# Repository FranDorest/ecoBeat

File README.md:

# EndeF-ecoBeat
EcoBeat is a device that measures the energy consumption by means of pulses. These pulses are generated by measuring equipment such as electricity, water or gas meters. EcoBeat translates the pulses to the corresponding units and transmits them via WIFI to a server on the Internet. This device complies with the Internet of Things standards and is specially designed to make energy measurements

# cable connection

## Optical pulse
- The pulse happens when the Interruption(6) is conected to  VCC(2)
- Interruption(6) -> pulldown

## Mechanical pulse
- The pulse happens when the Interruption(6) is conected to GND(5) 
- Interruption(6) -> pullup

## PCB Modification 
- 10K is disconected from GND and conected to Vcc

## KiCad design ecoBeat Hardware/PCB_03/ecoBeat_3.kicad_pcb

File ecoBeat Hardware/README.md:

# PCB ecoBeat 3

Se ha creado una nueva PCB que se adapta a las medidas de una caja de montaje en carril DIN.

### Materiales

A continuación aparecen los materiales que se necesitarán para construir la placa *ecoBeat*.

* [Soldador] 
* [Estaño]
* [Pinzas]
* [ESP 12 F](https://www.elecrow.com/download/ESP-12F.pdf) - Microcontrolador de 32-bit 
* [ATtiny 85](http://www.farnell.com/datasheets/1698186.pdf) - Microcontrolador de 8-bit
* [LM1117 3.3v](http://www.ti.com/lit/ds/symlink/lm1117.pdf) - Regulador de voltaje 15v - 3.3v 800mA
* [RJ45 8P8P Female](https://es.rs-online.com/web/p/conectores-rj45/2578814/) - Conector RJ45
* [2x Pulsador](https://www.adafruit.com/product/367) - Pulsador 6x6mm
* [4x 10k R](https://es.rs-online.com/web/p/resistencias-fijas-de-orificio-pasante/7077745/) - Resistencia 10k 1/4W
* [3x 220 R](https://es.rs-online.com/web/p/resistencias-fijas-de-orificio-pasante/7077612/) - Resistencia 220 1/4W
* [1x 12k R](https://es.rs-online.com/web/p/resistencias-fijas-de-orificio-pasante/7077735/) - Resistencia 12k 1/4W
* [1x 6.8k R](https://es.rs-online.com/web/p/resistencias-fijas-de-orificio-pasante/7077735/) - Resistencia 6.8k 1/4W
* [2x 10uF C](https://es.rs-online.com/web/p/condensadores-de-aluminio/0117035/) - Condensador electrolítico 10uF 50v
* [1x 100nF C](https://es.rs-online.com/web/p/condensadores-ceramicos-multicapa/5373707/) - Condensador cerámico 100nF 50v
* [1x Diodo](https://es.rs-online.com/web/p/products/7965985/?tpr=1) - Diodo 1A
* [3x LED](https://es.rs-online.com/web/p/led-visibles/2285944/) - LED 3mm
* [Pin macho 2.54mm](https://es.rs-online.com/web/p/conectores-macho-para-pcb/5473166/) - Tira pin Macho 2.54mm
* [Pin macho 2mm](https://es.rs-online.com/web/p/conectores-macho-para-pcb/6813293/) - Tira pin Macho 2mm
* [Pin hembra 2mm](https://es.rs-online.com/web/p/conectores-hembra-para-pcb/6058774/) - Tira pin hembra 2mm

### Montaje

*

## Herramientas

* [KiCad 4.0.2](http://kicad-pcb.org/) - Diseño electrónico

## Consumos

*Se ha realizado una prueba para conocer los consumos del equipo en todos sus modos de trabajo en su versión de 5V.

Modo | Con LEDs | Sin LEDs | Un
--- | --- | --- | ---
AP | 87 - 88 | 85-86 | mA 
--- | --- | --- | ---
STA + AP | 87 - 88 | 85-86 | mA
--- | --- | --- | ---
STA |85.5 - 86.5 | 3.5 - 84.5 | mA
--- | --- | --- | ---
Transmisión | 86.5 - 87.5 | 84.5 - 85.5 | mA

*Vmax 12V. El regulador se calentará hasta los 65ºC y consumirá 84,5mA.

## Autores

* **Francisco Doreste** 
* **Oscar Pujal** 

## Licencia

Este proyecto se encuentra bajo licencia GPL.

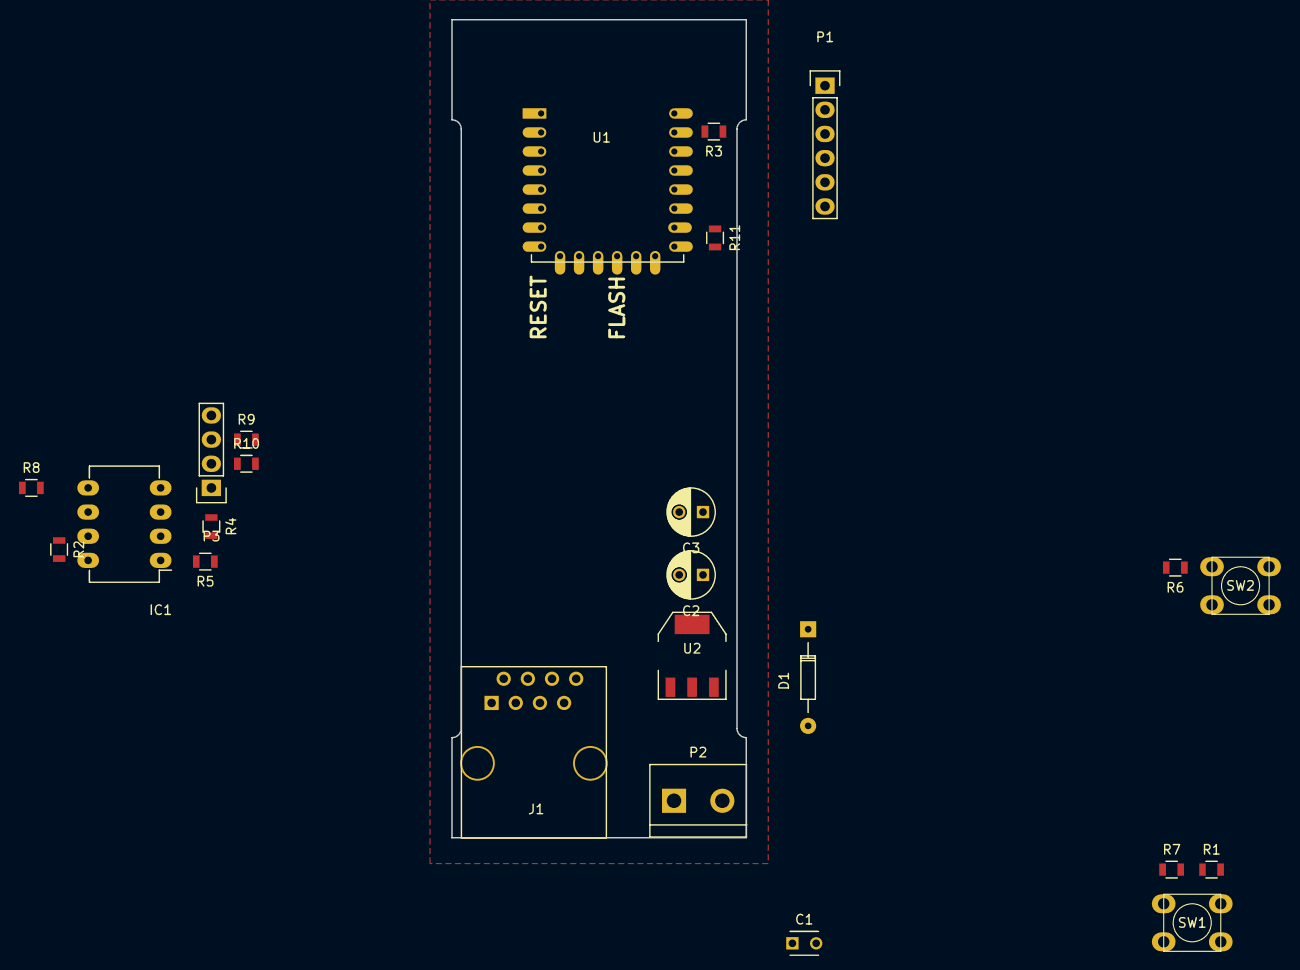
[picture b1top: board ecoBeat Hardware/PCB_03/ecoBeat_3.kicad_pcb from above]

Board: 2 copper layers, 30.9 x 86.0 mm, 24 parts (0 on the bottom side), 19 nets, no tracks yet.

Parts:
C1: 100nF; C_Disc_D3_P2.5
C2, C3: 10uF; C_Radial_D5_L6_P2.5
D1: D; Diode_DO-35_SOD27_Horizontal_RM10
IC1: ATTINY85-P; DIP-8_W7.62mm_LongPads
J1: RJ45; RJ45_8
P1: CONN_01X06; Pin_Header_Straight_1x06
P2: CONN_01X02; bornier2
P3: CONN_01X04; Pin_Header_Straight_1x04
R1, R2, R5, R6, R7, R11: 10k; R_0805
R3: 6.8k; R_0805
R4: 12k; R_0805
R8, R9, R10: 220; R_0805
SW1, SW2: SW_PUSH; SW_PUSH_SMALL
U1: ESP-12F; ESP-12E
U2: AP1117D33; SOT-223

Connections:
3.3: C1.1, C3.1, IC1.8, J1.2, P1.5, R1.1, R2.2, R5.1, R7.2, R10.2, U1.2, U1.8, U2.2
ESPRST: P1.1, R1.2, SW1.1, U1.1
GND: C1.2, C2.2, C3.2, IC1.4, J1.5, P1.6, P2.1, P3.1, R4.1, R11.2, SW1.2, SW2.2, U1.9, U2.1
INT1: IC1.6, U1.6
L1: IC1.5, R8.2
L2: R9.2, U1.4
unnamed: D1.2, P2.2
unnamed: IC1.7, J1.6, R2.1
unnamed: P1.3, R3.1
unnamed: P3.2, R10.1
unnamed: P3.3, R9.1
unnamed: P3.4, R8.1
unnamed: R6.1, SW2.1, U1.12
unnamed: R7.1, U1.3
unnamed: R11.1, U1.10
RSTTINY: IC1.1, R5.2, U1.5
RXD: IC1.2, R3.2, R4.2, U1.15
TXD: IC1.3, P1.2, U1.16
VCC: C2.1, D1.1, R6.2, U2.3

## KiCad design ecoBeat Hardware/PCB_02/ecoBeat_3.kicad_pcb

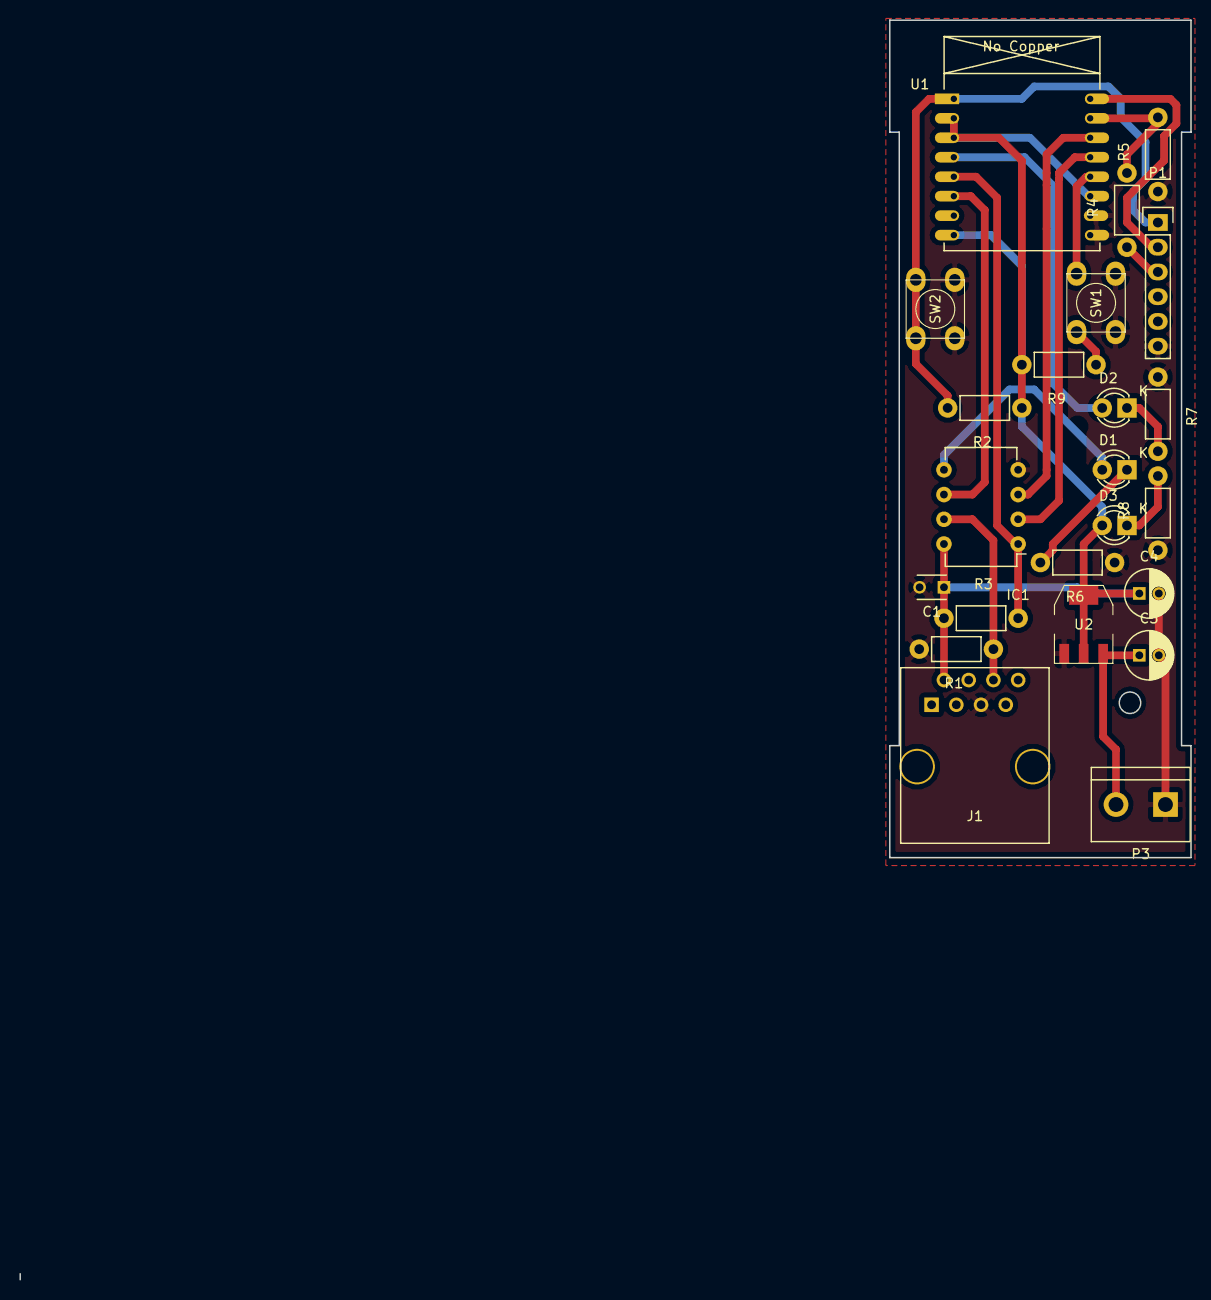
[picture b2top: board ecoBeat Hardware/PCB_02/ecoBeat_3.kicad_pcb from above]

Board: 2 copper layers, 30.9 x 86.0 mm, 23 parts (0 on the bottom side), 18 nets.

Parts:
C1: 100nF; C_Disc_D3_P2.5
C3, C4: 10uF; C_Radial_D5_L11_P2
D1, D2, D3: LED; LED-3MM
IC1: ATTINY85-P; DIP-8_W7.62mm
J1: RJ45; RJ45_8
P1: CONN_01X06; Pin_Header_Straight_1x06
P3: CONN_01X02; bornier2
R1, R2, R3, R9: 10k; Resistor_Horizontal_RM7mm
R4: 6.8k; Resistor_Horizontal_RM7mm
R5: 12k; Resistor_Horizontal_RM7mm
R6, R7, R8: 220; Resistor_Horizontal_RM7mm
SW1, SW2: SW_PUSH; SW_PUSH_SMALL
U1: ESP-12E; ESP-07v2
U2: AP1117D33; SOT-223

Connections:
ESPRST: P1.1, R2.2, SW2.1, U1.1
GND: C1.2, C3.2, C4.2, IC1.4, J1.5, P1.6, P3.1, R1.2, R5.1, R6.1, R7.1, R8.1, SW1.2, SW2.2, U1.9, U1.10, U2.1
INT1: IC1.6, U1.6
L1: D1.2, IC1.5
L2: D2.2, U1.4
unnamed: C3.1, P3.2, U2.3
unnamed: D1.1, R6.2
unnamed: D2.1, R7.2
unnamed: D3.1, R8.2
unnamed: IC1.7, J1.6, R1.1
unnamed: P1.3, R4.1
unnamed: R9.1, SW1.1, U1.12
RSTTINY: IC1.1, R3.2, U1.5
RX1: IC1.2, U1.13
RXD: R4.2, R5.2, U1.15
TX1: IC1.3, U1.14
TXD: P1.2, U1.16
VCC: C1.1, C4.1, D3.2, IC1.8, J1.2, R2.1, R3.1, R9.2, U1.2, U1.3, U1.8, U1.11, U2.2

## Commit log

2018-03-09 cambio
2018-03-13 Board 2
2018-03-14 rev2
2018-03-15 PCB_03
2018-03-15 gerber
2018-03-21 master
2018-04-05 1117 volteado
2018-04-20 cuenta pulsos totales
2018-05-05 mandado a fabricar PCBWay
2018-05-25 firmware 2
2018-06-01 lector de impulsos de contadores
2018-06-14 attiny Firmware_3_actualizacion
2018-06-20 envia pulso minuto
2018-06-21 Elimina Esp12 Firmware
2018-06-21 añade ESP12 Firmare (2.3)
2018-06-21 borrado ESP-12
2018-07-11 borrado sw para luego mezclar
2018-07-11 borrado hw para posteriormente mezclar
2018-07-11 incluido sw de fabricacion
2018-09-05 rj45 connection
2018-09-05 minor
2018-09-06 description
